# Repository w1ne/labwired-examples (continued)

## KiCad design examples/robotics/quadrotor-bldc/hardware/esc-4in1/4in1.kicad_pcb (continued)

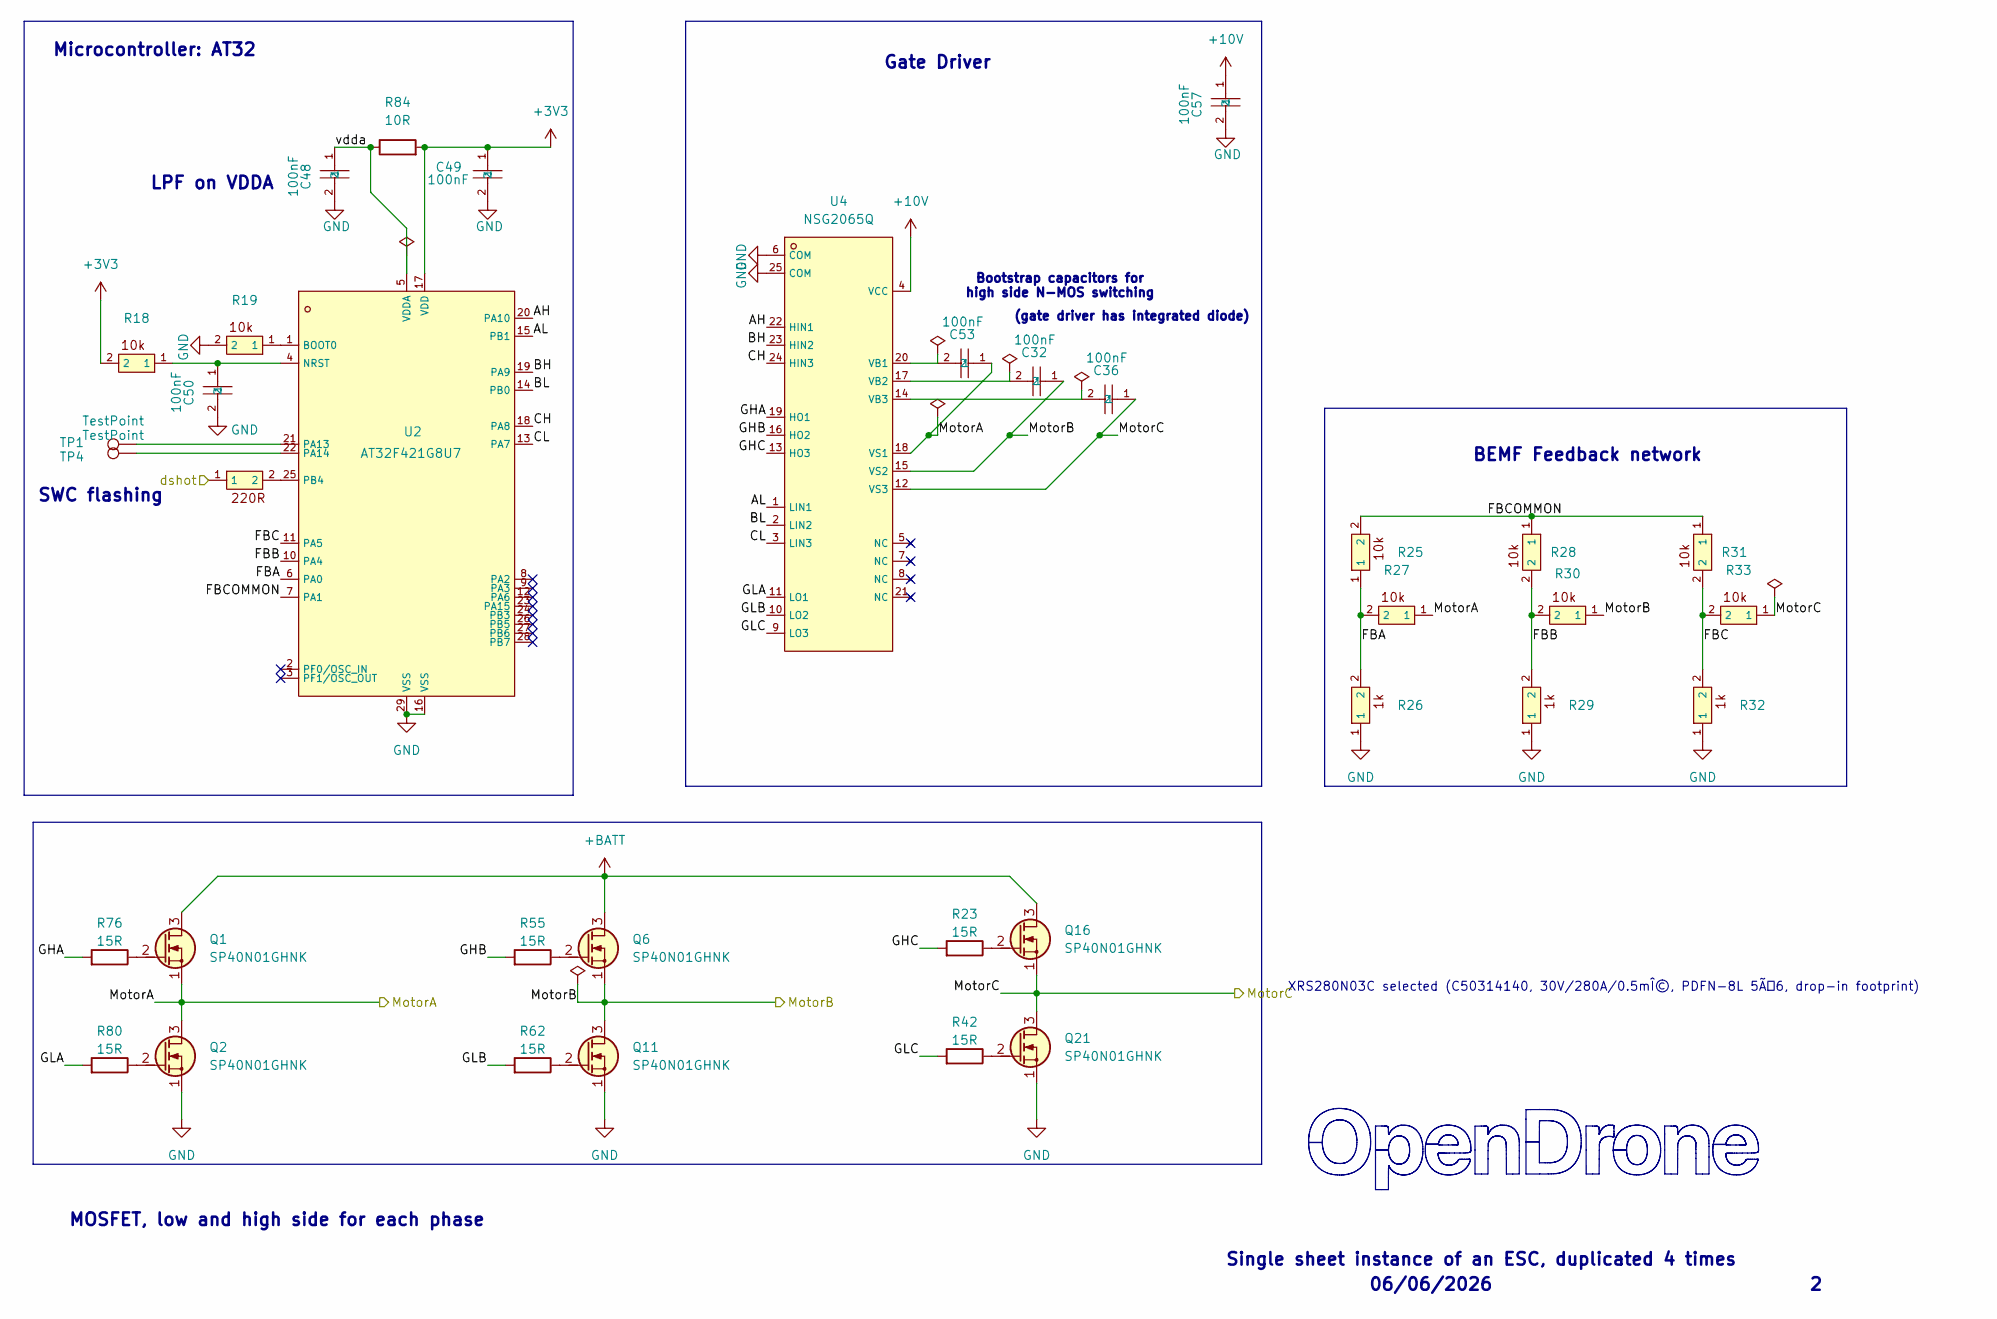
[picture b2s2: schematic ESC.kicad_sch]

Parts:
C32, C36, C53: 100nF; C_0402_WIDE; MPN CL05B104KB54PNC; LCSC C307331
C48, C49, C50, C57: 100nF; C_0201_0603Metric; MPN GRM033R6YA104KE14D; LCSC C181043
Q1, Q2, Q6, Q11, Q16, Q21: SP40N01GHNK; PDFN-8L_L6.0-W5.0-P1.27; MPN SP40N01GHNK; LCSC C22385416
R18, R19: 10k; R_0201_0603Metric; MPN RC0201FR-0710KL; LCSC C106225
R20: 220R; R_0201_0603Metric; MPN AC0201FR-07220RL; LCSC C226468
R23, R42, R55, R62, R76, R80: 15R; R_0201_0603Metric; MPN 0201WMF150JTEE; LCSC C473542
R25, R27, R28, R30, R31, R33: 10k; C_0201_0603Metric; MPN RC0201FR-0710KL; LCSC C106225
R26, R29, R32: 1k; C_0201_0603Metric; MPN 0201WMF1001TEE; LCSC C270365
R84: 10R; R_0201_0603Metric; MPN RC0201FR-0710RL; LCSC C106226
TP1, TP4: TestPoint; TestPoint_Pad_D1.0mm
U2: AT32F421G8U7; QFN-28_L4.0-W4.0-P0.40-TL-EP2.4; MPN AT32F421G8U7; LCSC C2765098
U4: NSG2065Q; QFN-24_L4.0-W4.0-P0.50-TL-EP2.8; MPN NSG2065Q; LCSC C41414478

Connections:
+3V3: C49.1, R18.2, R84.2, U2.17 (VDD); also elsewhere on the board
+10V: C57.1, U4.4 (VCC); also elsewhere on the board
+BATT: Q1.3 (D), Q6.3 (D), Q16.3 (D); also elsewhere on the board
/ESC1/AH: U2.20 (PA10), U4.22 (HIN1)
/ESC1/AL: U2.15 (PB1), U4.1 (LIN1)
/ESC1/BH: U2.19 (PA9), U4.23 (HIN2)
/ESC1/BL: U2.14 (PB0), U4.2 (LIN2)
/ESC1/CH: U2.18 (PA8), U4.24 (HIN3)
/ESC1/CL: U2.13 (PA7), U4.3 (LIN3)
/ESC1/FBA: R25.1, R26.2, R27.2, U2.6 (PA0)
/ESC1/FBB: R28.2, R29.2, R30.2, U2.10 (PA4)
/ESC1/FBC: R31.2, R32.2, R33.2, U2.11 (PA5)
/ESC1/FBCOMMON: R25.2, R28.1, R31.1, U2.7 (PA1)
/ESC1/GHA: R76.1, U4.19 (HO1)
/ESC1/GHB: R55.1, U4.16 (HO2)
/ESC1/GHC: R23.1, U4.13 (HO3)
/ESC1/GLA: R80.1, U4.11 (LO1)
/ESC1/GLB: R62.1, U4.10 (LO2)
/ESC1/GLC: R42.1, U4.9 (LO3)
/ESC1/MotorA: C53.1, Q1.1 (S), Q2.3 (D), R27.1, U4.18 (VS1); also elsewhere on the board
/ESC1/MotorB: C32.1, Q6.1 (S), Q11.3 (D), R30.1, U4.15 (VS2); also elsewhere on the board
/ESC1/MotorC: C36.1, Q16.1 (S), Q21.3 (D), R33.1, U4.12 (VS3); also elsewhere on the board
/ESC1/vdda: C48.1, R84.1, U2.5 (VDDA)
/M1: R20.1; also elsewhere on the board
GND: C48.2, C49.2, C50.2, C57.2, Q2.1 (S), Q11.1 (S), Q21.1 (S), R19.2, R26.1, R29.1, R32.1, U2.16 (VSS), U2.29 (VSS), U4.6 (COM), U4.25 (COM); also elsewhere on the board
unnamed: Q1.2 (G), R76.2
unnamed: Q2.2 (G), R80.2
unnamed: Q6.2 (G), R55.2
unnamed: Q11.2 (G), R62.2
unnamed: Q16.2 (G), R23.2
unnamed: Q21.2 (G), R42.2
unnamed: R19.1, U2.1 (BOOT0)
unnamed: C50.1, R18.1, U2.4 (NRST)
unnamed: TP1.1 (1_1), U2.21 (PA13)
unnamed: TP4.1 (1_1), U2.22 (PA14)
unnamed: R20.2, U2.25 (PB4)
unnamed: C53.2, U4.20 (VB1)
unnamed: C32.2, U4.17 (VB2)
unnamed: C36.2, U4.14 (VB3)

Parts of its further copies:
C33, C34, C35, C37, C38, C39, C56, C62, C67: 100nF; C_0402_WIDE; MPN CL05B104KB54PNC; LCSC C307331
C52, C54, C55, C58, C59, C60, C61, C63, C64, C65, C66, C68: 100nF; C_0201_0603Metric; MPN GRM033R6YA104KE14D; LCSC C181043
Q3, Q4, Q5, Q7, Q8, Q9, Q10, Q12, Q13, Q14, Q15, Q17, Q18, Q19, Q20, Q22, Q23, Q24: SP40N01GHNK; PDFN-8L_L6.0-W5.0-P1.27; MPN SP40N01GHNK; LCSC C22385416
R10, R12, R13, R15, R34, R36, R46, R48, R49, R51, R52, R54, R64, R66, R67, R69, R70, R72: 10k; C_0201_0603Metric; MPN RC0201FR-0710KL; LCSC C106225
R11, R14, R35, R47, R50, R53, R65, R68, R71: 1k; C_0201_0603Metric; MPN 0201WMF1001TEE; LCSC C270365
R21, R22, R40, R41, R58, R59: 10k; R_0201_0603Metric; MPN RC0201FR-0710KL; LCSC C106225
R24, R37, R38, R43, R44, R45, R56, R60, R61, R63, R74, R75, R77, R78, R79, R81, R82, R83: 15R; R_0201_0603Metric; MPN 0201WMF150JTEE; LCSC C473542
R39, R57, R87: 220R; R_0201_0603Metric; MPN AC0201FR-07220RL; LCSC C226468
R85, R86, R88: 10R; R_0201_0603Metric; MPN RC0201FR-0710RL; LCSC C106226
TP2, TP3, TP5, TP6, TP7, TP8: TestPoint; TestPoint_Pad_D1.0mm
U5, U7, U9: AT32F421G8U7; QFN-28_L4.0-W4.0-P0.40-TL-EP2.4; MPN AT32F421G8U7; LCSC C2765098
U6, U8, U10: NSG2065Q; QFN-24_L4.0-W4.0-P0.50-TL-EP2.8; MPN NSG2065Q; LCSC C41414478

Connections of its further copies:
+3V3: C55.1, C61.1, C66.1, R21.2, R40.2, R58.2, R85.2, R86.2, R88.2, U5.17 (VDD), U7.17 (VDD), U9.17 (VDD); also elsewhere on the board
+10V: C58.1, C63.1, C68.1, U6.4 (VCC), U8.4 (VCC), U10.4 (VCC); also elsewhere on the board
+BATT: Q7.3 (D), Q8.3 (D), Q9.3 (D), Q10.3 (D), Q13.3 (D), Q17.3 (D), Q18.3 (D), Q19.3 (D), Q20.3 (D); also elsewhere on the board
/ESC2/AH: U5.20 (PA10), U6.22 (HIN1)
/ESC2/AL: U5.15 (PB1), U6.1 (LIN1)
/ESC2/BH: U5.19 (PA9), U6.23 (HIN2)
/ESC2/BL: U5.14 (PB0), U6.2 (LIN2)
/ESC2/CH: U5.18 (PA8), U6.24 (HIN3)
/ESC2/CL: U5.13 (PA7), U6.3 (LIN3)
/ESC2/FBA: R10.1, R11.2, R12.2, U5.6 (PA0)
/ESC2/FBB: R13.2, R14.2, R15.2, U5.10 (PA4)
/ESC2/FBC: R34.2, R35.2, R36.2, U5.11 (PA5)
/ESC2/FBCOMMON: R10.2, R13.1, R34.1, U5.7 (PA1)
/ESC2/GHA: R77.1, U6.19 (HO1)
/ESC2/GHB: R56.1, U6.16 (HO2)
/ESC2/GHC: R24.1, U6.13 (HO3)
/ESC2/GLA: R81.1, U6.11 (LO1)
/ESC2/GLB: R63.1, U6.10 (LO2)
/ESC2/GLC: R43.1, U6.9 (LO3)
/ESC2/MotorA: C56.1, Q3.3 (D), Q7.1 (S), R12.1, U6.18 (VS1); also elsewhere on the board
/ESC2/MotorB: C33.1, Q8.1 (S), Q12.3 (D), R15.1, U6.15 (VS2); also elsewhere on the board
/ESC2/MotorC: C37.1, Q17.1 (S), Q22.3 (D), R36.1, U6.12 (VS3); also elsewhere on the board
/ESC2/vdda: C54.1, R85.1, U5.5 (VDDA)
/ESC3/AH: U7.20 (PA10), U8.22 (HIN1)
/ESC3/AL: U7.15 (PB1), U8.1 (LIN1)
/ESC3/BH: U7.19 (PA9), U8.23 (HIN2)
/ESC3/BL: U7.14 (PB0), U8.2 (LIN2)
/ESC3/CH: U7.18 (PA8), U8.24 (HIN3)
/ESC3/CL: U7.13 (PA7), U8.3 (LIN3)
/ESC3/FBA: R46.1, R47.2, R48.2, U7.6 (PA0)
/ESC3/FBB: R49.2, R50.2, R51.2, U7.10 (PA4)
/ESC3/FBC: R52.2, R53.2, R54.2, U7.11 (PA5)
/ESC3/FBCOMMON: R46.2, R49.1, R52.1, U7.7 (PA1)
/ESC3/GHA: R78.1, U8.19 (HO1)
/ESC3/GHB: R60.1, U8.16 (HO2)
/ESC3/GHC: R37.1, U8.13 (HO3)
/ESC3/GLA: R82.1, U8.11 (LO1)
/ESC3/GLB: R74.1, U8.10 (LO2)
/ESC3/GLC: R44.1, U8.9 (LO3)
/ESC3/MotorA: C62.1, Q4.3 (D), Q13.1 (S), R48.1, U8.18 (VS1); also elsewhere on the board
/ESC3/MotorB: C34.1, Q9.1 (S), Q14.3 (D), R51.1, U8.15 (VS2); also elsewhere on the board
/ESC3/MotorC: C38.1, Q18.1 (S), Q23.3 (D), R54.1, U8.12 (VS3); also elsewhere on the board
/ESC3/vdda: C60.1, R86.1, U7.5 (VDDA)
/ESC4/AH: U9.20 (PA10), U10.22 (HIN1)
/ESC4/AL: U9.15 (PB1), U10.1 (LIN1)
/ESC4/BH: U9.19 (PA9), U10.23 (HIN2)
/ESC4/BL: U9.14 (PB0), U10.2 (LIN2)
/ESC4/CH: U9.18 (PA8), U10.24 (HIN3)
/ESC4/CL: U9.13 (PA7), U10.3 (LIN3)
/ESC4/FBA: R64.1, R65.2, R66.2, U9.6 (PA0)
/ESC4/FBB: R67.2, R68.2, R69.2, U9.10 (PA4)
/ESC4/FBC: R70.2, R71.2, R72.2, U9.11 (PA5)
/ESC4/FBCOMMON: R64.2, R67.1, R70.1, U9.7 (PA1)
/ESC4/GHA: R79.1, U10.19 (HO1)
/ESC4/GHB: R61.1, U10.16 (HO2)
/ESC4/GHC: R38.1, U10.13 (HO3)
/ESC4/GLA: R83.1, U10.11 (LO1)
/ESC4/GLB: R75.1, U10.10 (LO2)
/ESC4/GLC: R45.1, U10.9 (LO3)
/ESC4/MotorA: C67.1, Q5.3 (D), Q19.1 (S), R66.1, U10.18 (VS1); also elsewhere on the board
/ESC4/MotorB: C35.1, Q10.1 (S), Q15.3 (D), R69.1, U10.15 (VS2); also elsewhere on the board
/ESC4/MotorC: C39.1, Q20.1 (S), Q24.3 (D), R72.1, U10.12 (VS3); also elsewhere on the board
/ESC4/vdda: C65.1, R88.1, U9.5 (VDDA)
/M2: R39.1; also elsewhere on the board
/M3: R57.1; also elsewhere on the board
/M4: R87.1; also elsewhere on the board
GND: C52.2, C54.2, C55.2, C58.2, C59.2, C60.2, C61.2, C63.2, C64.2, C65.2, C66.2, C68.2, Q3.1 (S), Q4.1 (S), Q5.1 (S), Q12.1 (S), Q14.1 (S), Q15.1 (S), Q22.1 (S), Q23.1 (S), Q24.1 (S), R11.1, R14.1, R22.2, R35.1, R41.2, R47.1, R50.1, R53.1, R59.2, R65.1, R68.1, R71.1, U5.16 (VSS), U5.29 (VSS), U6.6 (COM), U6.25 (COM), U7.16 (VSS), U7.29 (VSS), U8.6 (COM), U8.25 (COM), U9.16 (VSS), U9.29 (VSS), U10.6 (COM), U10.25 (COM); also elsewhere on the board
unnamed: Q3.2 (G), R81.2
unnamed: Q4.2 (G), R82.2
unnamed: Q5.2 (G), R83.2
unnamed: Q7.2 (G), R77.2
unnamed: Q8.2 (G), R56.2
unnamed: Q9.2 (G), R60.2
unnamed: Q10.2 (G), R61.2
unnamed: Q12.2 (G), R63.2
unnamed: Q13.2 (G), R78.2
unnamed: Q14.2 (G), R74.2
unnamed: Q15.2 (G), R75.2
unnamed: Q17.2 (G), R24.2
unnamed: Q18.2 (G), R37.2
unnamed: Q19.2 (G), R79.2
unnamed: Q20.2 (G), R38.2
unnamed: Q22.2 (G), R43.2
unnamed: Q23.2 (G), R44.2
unnamed: Q24.2 (G), R45.2
unnamed: R22.1, U5.1 (BOOT0)
unnamed: C52.1, R21.1, U5.4 (NRST)
unnamed: TP2.1 (1_1), U5.21 (PA13)
unnamed: TP5.1 (1_1), U5.22 (PA14)
unnamed: R39.2, U5.25 (PB4)
unnamed: C56.2, U6.20 (VB1)
unnamed: C33.2, U6.17 (VB2)
unnamed: C37.2, U6.14 (VB3)
unnamed: R41.1, U7.1 (BOOT0)
unnamed: C59.1, R40.1, U7.4 (NRST)
unnamed: TP3.1 (1_1), U7.21 (PA13)
unnamed: TP6.1 (1_1), U7.22 (PA14)
unnamed: R57.2, U7.25 (PB4)
unnamed: C62.2, U8.20 (VB1)
unnamed: C34.2, U8.17 (VB2)
unnamed: C38.2, U8.14 (VB3)
unnamed: R59.1, U9.1 (BOOT0)
unnamed: C64.1, R58.1, U9.4 (NRST)
unnamed: TP7.1 (1_1), U9.21 (PA13)
unnamed: TP8.1 (1_1), U9.22 (PA14)
unnamed: R87.2, U9.25 (PB4)
unnamed: C67.2, U10.20 (VB1)
unnamed: C35.2, U10.17 (VB2)
unnamed: C39.2, U10.14 (VB3)

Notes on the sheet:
Single sheet instance of an ESC, duplicated 4 times
MOSFET, low and high side for each phase
Gate Driver
SWC flashing
XRS280N03C selected (C50314140, 30V/280A/0.5mÎ©, PDFN-8L 5Ã6, drop-in footprint)
Bootstrap capacitors for high side N-MOS switching
BEMF Feedback network
(gate driver has integrated diode)
Microcontroller: AT32
LPF on VDDA
06/06/2026

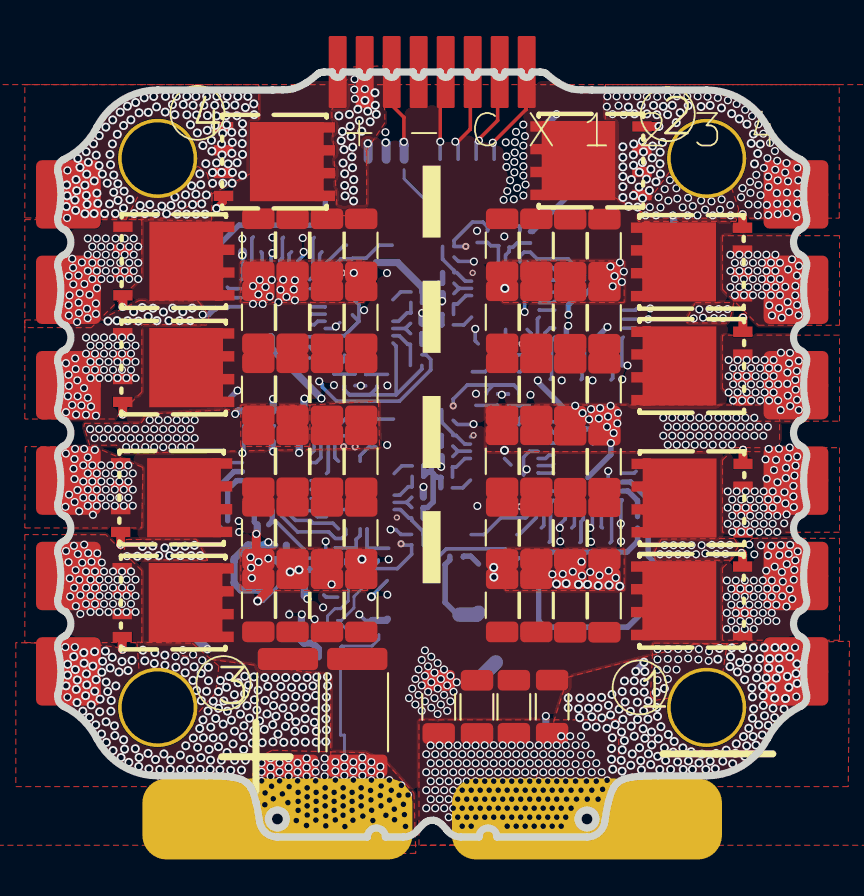
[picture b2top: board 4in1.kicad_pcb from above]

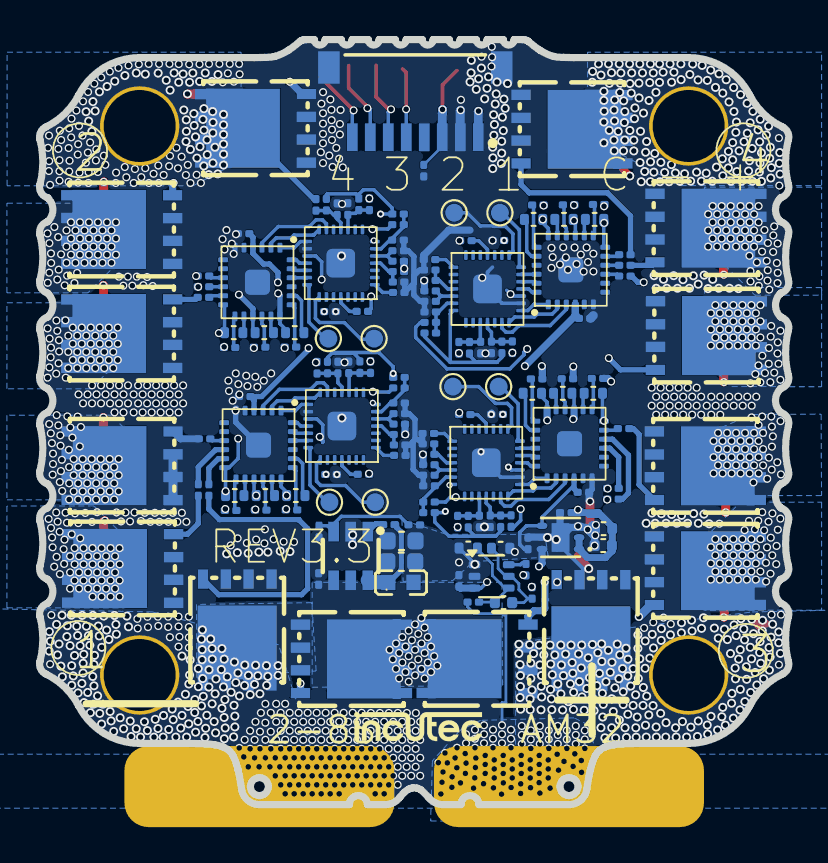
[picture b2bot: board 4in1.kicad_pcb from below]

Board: 6 copper layers, 41.6 x 42.5 mm, 222 parts (157 on the bottom side), 152 nets.

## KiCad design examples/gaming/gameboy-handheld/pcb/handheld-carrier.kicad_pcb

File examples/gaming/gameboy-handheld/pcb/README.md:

# Handheld carrier PCB

The routed two-layer carrier passes KiCad 9.0.2 DRC with **0 violations and 0 unconnected items**. The board is an engineering prototype. No physical PCB or assembled handheld has been tested.

## Files

- `handheld-carrier.kicad_pcb`: authoritative routed board, pads, nets and filled copper.
- `handheld-carrier.kicad_pro`: KiCad project settings used for DRC.
- `bom.csv` / `positions.csv`: assembly proposal and footprint origins.
- `carrier-layout.json`: physical pads, nets and transform to the shared case coordinate system.
- `simulation-binding.json`: correspondence between PCB references and the verified LabWired circuit.
- `drc-routed.json` / `routing-report.json`: exact checks and source hashes.
- `export-validation.json`: final Gerber, drill and STEP byte/hash verification, all 124 drill coordinates, and the exact PCB/layout/interface identities.
- `final-import-report.json`: current LabWired design-context coverage bound to the final native PCB hash.
- `native-preserve-preflight/`: exact-source local preservation, generated rules and independent KiCad DRC evidence.
- `hosted-native-integration/`: production source/rules readback, separate hosted KiCad DRC and the verified owner project attachment.
- `import-report.json`: historical import coverage before the connector correction.

Generated fabrication and plot binaries are omitted from this compact contribution. Use the editable routed board to regenerate Gerber, drill, STEP and layer plots in KiCad 9 after rerunning DRC.

## Electrical and mechanical design

The carrier measures 78 × 132 mm with two copper layers and a nominal 1.6 mm substrate. It has 16 footprints: one rear-mounted WeAct Black Pill, one LCD cable header, eight buttons, two bypass capacitors and four mounting holes. The carrier uses 0.25 mm signal tracks, 0.6 / 0.3 mm vias, at least 0.2 mm track clearance and 0.25 mm copper-plane clearance. KiCad fills the ground planes and checks the final geometry.

The module footprint comes from WeAct's published Black Pill v3 KiCad library. The physical module has two 20-pin headers on a 15.24 mm row spacing, plus four optional SWD pins. The carrier main-header holes are 1.02 mm nominal for two Samtec TSW-120-07-G-S strips, following the manufacturer's recommended PCB footprint. The upstream vendor file remains unchanged; the carrier generator applies the selected assembly hole sizes. The four optional SWD positions remain unpopulated. The duplicate power pins are connected on the module; the carrier assigns the required rail pads and leaves unused GPIO pads unconnected.

J1 uses the JST B8B-PH-K-S(LF)(SN) vertical 8-pin header at 2.0 mm pitch. Pin 1 is at PCB (32, 64) mm, below the LCD envelope; the original (56, 17) mm position put the mated connector under the display. Its required signal order is VCC, GND, DIN, CLK/SCK, CS, DC, RST, BL. The official module schematic assigns the same signal sequence; this does not establish the supplied cable wiring or housing orientation. The LCD itself mounts above the PCB. It is not a generic 8-pin footprint soldered directly to the carrier.

The shared interface uses rear-bottom-center case coordinates. The PCB transform is `case_x = pcb_x - 39`, `case_y = 140 - pcb_y`; the nominal PCB center plane is `case_z = 14.2 mm`. Four 2.8 mm holes lie at case x ±29 mm, y 16 / 132 mm. Four concave 4.3 mm radius corner notches clear the case closure posts. The notch arcs are sampled with less than 0.01 mm chord error. The nearest hole-to-notch material web is approximately 2.36 mm.

Power enters the Black Pill through USB. The proposed enclosure gives direct access to the module USB-C connector; the separate extension/pigtail is no longer in the assembly proposal. The LCD receives 3.3 V from the module regulator. The design does not include a battery, charging circuit, speaker driver or cartridge socket.

## Checks and remaining limits

The current DRC report checks the complete routed KiCad board. It is not a schematic ERC result. The PCB pad netlist and `simulation-binding.json` provide the electrical handoff. The final mount coordinates match `../design-interfaces.json`. The current detailed assembly and its exact PCB source identity are recorded in `../kernelcad-reference.json`.

The PCB has not been ordered or assembled. Before fabrication, measure the purchased Black Pill, LCD cable and switch actuator heights. Check USB plug access, regulator current margin, display backlight current, cable exit, mechanical clearances and soldering access. The CAD uses component envelopes and does not establish exact component or connector fit.

A fresh `labwired_import` of the final native PCB accepts the design context but does not map the WeAct module or these switch footprints to a runnable twin. It maps the two capacitors, marks nine components design-only and ignores five non-simulated connectors or mounting holes. `final-import-report.json` records the exact source hash and result: `mode: design_only`, `twin_buildable: false`.

The final connector-corrected board passes both the local preflight in `native-preserve-preflight/` and the later independent hosted KiCad 9.0.2 DRC in `hosted-native-integration/`. The normal owner API attached `pcb_c8da1d7776dba9bc`, revision 0, on 2026-11-11 at 14:49 UTC. Downloaded PCB and rule artifacts match the exact authored/preflight bytes. The fresh attachment comparison changed only `pcb_board_id` and `pcb_board_rev`; editable source, circuit, stimuli, CAD revision and unlisted visibility were preserved. The stored import record reports routing and DRC as not run because preservation and independent validation are separate operations. The runnable circuit continues to use the explicit simulation binding; native import does not automatically create its MCU models.

## Rebuild

The generators require Python with KiCad 9 `pcbnew` and NumPy. On Debian-based KiCad installations, use the distribution Python interpreter:

```sh
/usr/bin/python3 build_carrier.py
/usr/bin/python3 route_carrier.py
kicad-cli pcb drc --format json -o drc-routed.json handheld-carrier.kicad_pcb
```

`build_carrier.py` reads the shared interface file. `route_carrier.py` uses a clearance-aware two-layer grid for the signal routes, adds the ground escape/stitch, then fills the ground planes. KiCad DRC is the authority; rerun DRC after every regeneration and before exporting fabrication files.

## Sources

- [WeAct Black Pill hardware library and pinout](https://github.com/WeActStudio/WeActStudio.MiniSTM32F4x1/tree/master/Hardware/KiCAD)
- [Waveshare 2.4-inch ILI9341 module interface and outline](https://www.waveshare.com/wiki/2.4inch_LCD_Module)
- Stock KiCad 9 footprint libraries for JST PH, 6 mm switches and capacitors.

The WeAct vendor files retain their upstream content. The KiCad 9 adaptation changes only the file version and removes the KiCad 10-only `duplicate_pad_numbers_are_jumpers` field. No pin number, pad position, or module outline was changed by that compatibility edit.

## Header and backlight interface review

`assembly-interfaces.json` records the selected header candidate and the official display schematic. The 40 main header holes changed from 0.8 mm to the Samtec-recommended 1.02 mm. The old hole was smaller than the nominal 0.898 mm diagonal of a 0.635 mm square terminal. That earlier header-only correction left copper, pad centers, net assignments and placement unchanged; the later connector relocation is recorded separately below. KiCad 9.0.2 DRC was rerun and reports zero violations and zero unconnected items. The nominal annular ring on the narrow pad axis is 0.29 mm.

The Samtec footprint gives the nominal hole size; it does not establish finished-hole tolerance. The terminal section is a reference dimension in its marketing drawing. Confirm the manufactured hole limits, purchased module holes, terminal tolerance, module thickness, seating and solder access. The selected strips are not validated for the purchased WeAct V3.0 module. Their nominal 0.898026 mm pin diagonal would leave only 0.001974 mm diametral clearance in a 0.9 mm module hole, before tolerances. Confirm module-side insertion fit separately from the carrier-side 1.02 mm nominal-hole choice.

The [Waveshare schematic](https://files.waveshare.com/upload/1/18/2.4inch_LCD_Module_Sch.pdf) shows BL feeding the base of U2 through R5 (1 kOhm), with a 10 kOhm pull-up and four separate 39 Ohm LED cathode resistors. PA8 therefore controls the module transistor; it does not supply raw LED current. This applies to that Waveshare module. Regulator and backlight current margins still need measurement.

Header sources: [TSW-120-07-G-S](https://www.samtec.com/products/tsw-120-07-g-s), [Samtec drawing](https://suddendocs.samtec.com/prints/tsw-xxx-xx-xxx-x-xx-xxx-mkt.pdf), and [recommended PCB footprint](https://suddendocs.samtec.com/prints/tsw-xxx-xx-x-x-xx-xxx-footprint.pdf).

## LCD header and control-switch review

The selected **JST B8B-PH-K-S(LF)(SN)** has nominal 0.5 mm square, kinked terminals and a 3.4 mm reference tail. The general catalog hole drawing is 0.7 +0.1/0 mm, but it explicitly requires consideration of larger holes for fiberglass boards. JST's material-specific FAQ recommends **0.85-0.90 mm finished plated holes** for 3-16 circuit PH headers on glass-epoxy PCBs. J1 therefore uses a centered **0.875 mm nominal CAD/Excellon target**. This is a design requirement, not a measured finished hole or a prescription for the fabricator's pre-plating drill. The fabricator must select drill compensation and confirm the 0.85-0.90 mm final range, 2.00 mm pitch with non-accumulating ±0.05 mm positional tolerance, and annular ring after registration and etch tolerances. The 1.20 mm narrow pad dimension gives a nominal 0.1625 mm annular ring, or 0.15 mm at the largest specified finished hole; the board's design minimum is 0.10 mm.

The J1 header body is 17.9 × 4.5 × 6 mm. The sourced PHR-8 mating-envelope reference gives an 8 mm mated height. The connector now sits below the LCD, with a local support-plate notch and a separate wire-exit reservation in the mechanical assembly. Those reservations do not establish the bend radius or strain relief of the supplied cable. Confirm the purchased housing, crimp, pin order and cable routing.

The selected switch is **Omron B3F-1000**. Its 6.5 ±0.1 × 4.5 ±0.1 mm hole pattern matches the carrier. In the datasheet top view, terminals 4-3 form one horizontal common pair and 2-1 form the other; these match the carrier's two duplicate-pad groups. The footprint's pad numbers 1/2 represent electrical groups, not the manufacturer's four terminal numbers. The carrier now uses the centered 1.0 mm nominal hole recommendation with a 0.9-1.1 mm finished-hole acceptance range. The 4.3 ±0.2 mm actuator height and 0.15-0.45 mm pretravel are recorded for the enclosure. Generic 6 mm tactile switches are unsupported until their own drawings are checked.

The connector relocation reroutes 3V3, GND, PA4, PA5, PA7, PB0, PB1 and PA8. PB9 and PB10 each receive one local same-layer dogleg between PCB y = 61.5 and 66.5 mm because their prior paths intersected the new J1 pad row. The remaining six button-net track/via geometries, all other component positions and all pad-net identities are retained. The ground escape is reserved before signal routing. Final DRC reports zero violations and zero unconnected items. `connector-correction.json` records the before/after source identity, placement and hole changes, retained-copper checks and final DRC. The two central silkscreen labels move below the relocated connector.

For an incremental route after an explicit board-placement edit, the existing example router accepts `--input <board.kicad_pcb> --nets <net names>`. It removes only selected-net tracks, reserves the retained tracks/vias as obstacles, and refills the existing ground zones. A full clean rebuild still uses the default unrouted input.

Primary sources: [JST current PH catalog](https://www.jst-mfg.com/product/pdf/eng/ePH.pdf), [JST finished-hole guidance](https://www.jst.com/resources/faq/), [JST terminal drawing (manufacturer PDF mirrored by Pololu)](https://www.pololu.com/file/0J373/JST_ePH.pdf), and [Omron B3F datasheet](https://omronfs.omron.com/en_US/ecb/products/pdf/en-b3f.pdf). See `assembly-interfaces.json` for exact dimensions, sources and limits.

## LCD harness assembly

Waveshare supplies a [PH2.0 8-pin 20 cm cable](https://www.waveshare.com/2.4inch-LCD-Module.htm). That description does not establish a PH-to-PH assembly compatible with this carrier. The included controller-end GPIO sockets require re-termination. Retain the LCD-end plug and terminate the eight conductors into **one JST PHR-8** carrier housing. **Eight new SPH-002T-P0.5S contacts** are candidates only if the actual conductors are AWG 30-24 (0.05-0.22 mm²) with 0.8-1.5 mm insulation diameter, as specified in the JST catalog. Verify the supplied wire and correct crimp process; use a compatible replacement wire/contact assembly if those limits do not match.

| Carrier J1 pad | Carrier net | LCD signal contact | LCD function |
| --- | --- | --- | --- |
| 1 | 3V3 | 1 | VCC |
| 2 | GND | 2 | GND |
| 3 | PA7 | 3 | DIN |
| 4 | PA5 | 4 | SCK / CLK |
| 5 | PA4 | 5 | CS |
| 6 | PB0 | 6 | DC |
| 7 | PB1 | 7 | RST |
| 8 | PA8 | 8 | BL |

This table specifies the required endpoint continuity from the [official LCD schematic](https://files.waveshare.com/upload/1/18/2.4inch_LCD_Module_Sch.pdf), where the PH connector is J2 and the parallel header J1 has the same signal numbers. It does not assume an existing cable is straight-through. Identify each conductor by continuity to the actual LCD pin/function and identify housing pin 1 from the mating-face drawing/mark. Wire colors and left-to-right viewing order are not sufficient. With the harness disconnected and unpowered, verify the eight intended connections and isolation between every other conductor, then confirm the actual VCC/GND labels before mating.

The harness has not been assembled or tested. Its supplied 200 mm length, exit, bend radius and strain relief are not yet validated in the enclosure. The mechanical wire-exit reservation is a design allowance, not a vendor bend limit. `assembly-interfaces.json` contains the same endpoint map and assembly requirements.

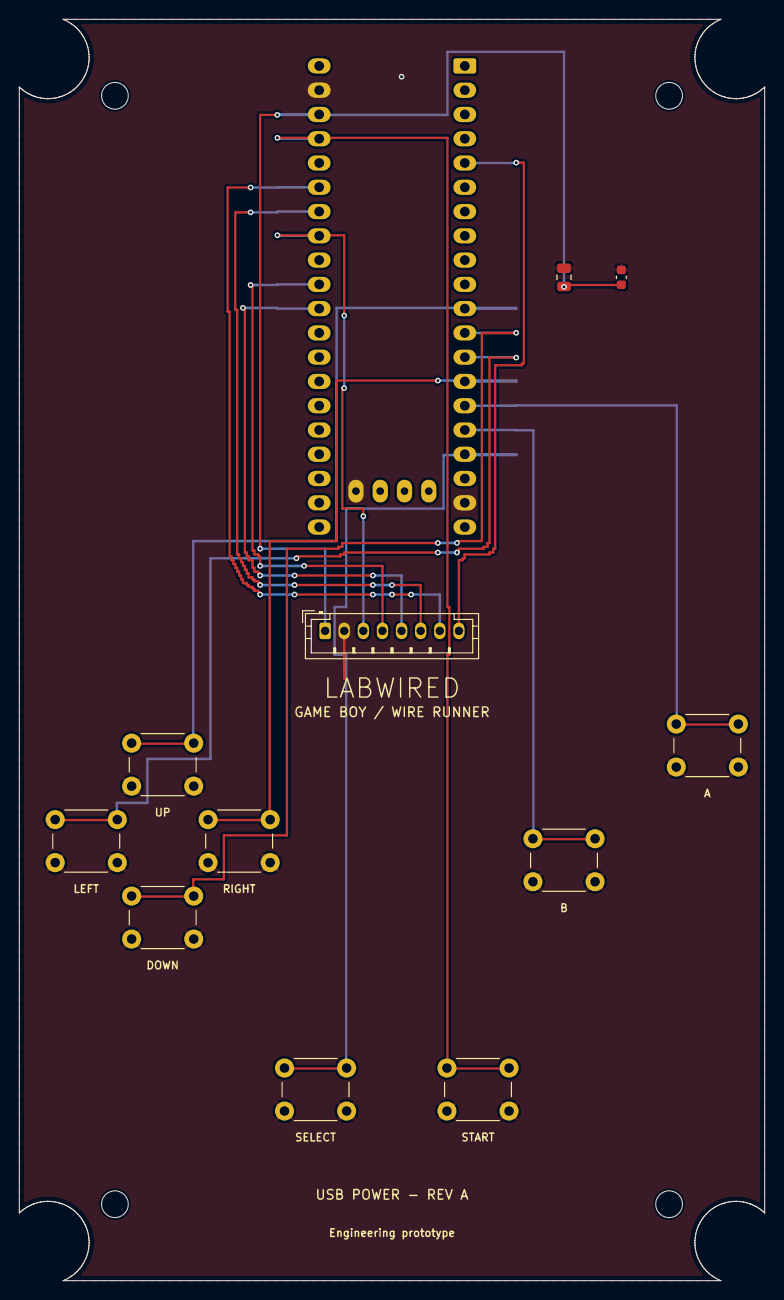
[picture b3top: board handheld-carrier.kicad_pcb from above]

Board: 2 copper layers, 78.0 x 132.0 mm, 16 parts (1 on the bottom side), 16 nets.

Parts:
A1: WeAct Black Pill STM32F411CEU6; WeAct-BlackPill-v3-kicad9
C1: 10uF 6.3V X7R; C_0805_2012Metric
C2: 100nF 16V X7R; C_0603_1608Metric
H1, H2, H3, H4: (no value)
J1: Waveshare LCD PH2.0 cable; JST_PH_B8B-PH-K_1x08_P2.00mm_Vertical
SW1: UP; SW_PUSH_6mm
SW2: DOWN; SW_PUSH_6mm
SW3: LEFT; SW_PUSH_6mm
SW4: RIGHT; SW_PUSH_6mm
SW5: A; SW_PUSH_6mm
SW6: B; SW_PUSH_6mm
SW7: SELECT; SW_PUSH_6mm
SW8: START; SW_PUSH_6mm

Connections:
3V3: A1.38, C1.1, C2.1, J1.1
GND: A1.19, A1.39, A1.44, C1.2, C2.2, J1.2, SW1.2, SW2.2, SW3.2, SW4.2, SW5.2, SW6.2, SW7.2, SW8.2
PA4: A1.30, J1.5
PA5: A1.31, J1.4
PA7: A1.33, J1.3
PA8: A1.5, J1.8
PB0: A1.34, J1.6
PB1: A1.35, J1.7
PB3: A1.11, SW1.1
PB4: A1.12, SW2.1
PB5: A1.13, SW3.1
PB6: A1.14, SW4.1
PB7: A1.15, SW5.1
PB8: A1.16, SW6.1
PB9: A1.17, SW7.1
PB10: A1.37, SW8.1
